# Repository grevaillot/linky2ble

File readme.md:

# linky2ble

stm32wb55 based linky teleinfo to ble bridge - based on https://fumeebleue.fr/ & https://hallard.me/pitinfov12/ designs

## Preview:

## Schematics:

## Aisler project:

https://aisler.net/p/WQYUVWAP (ordering a stencil is recommended :))

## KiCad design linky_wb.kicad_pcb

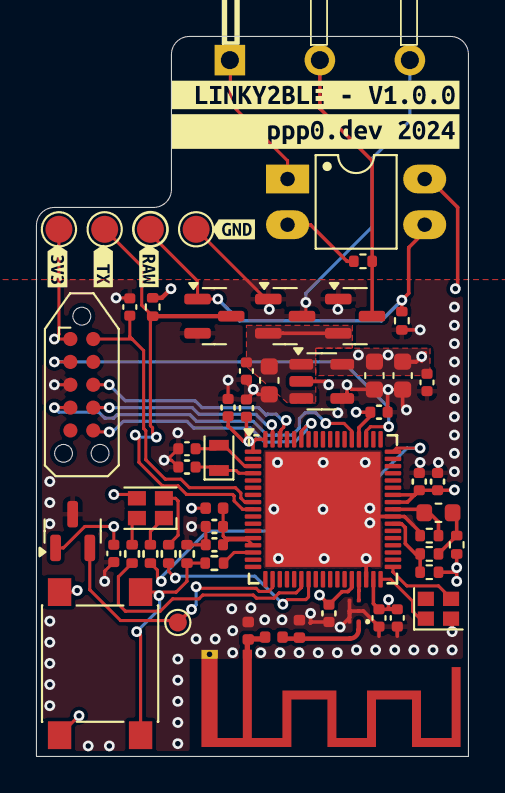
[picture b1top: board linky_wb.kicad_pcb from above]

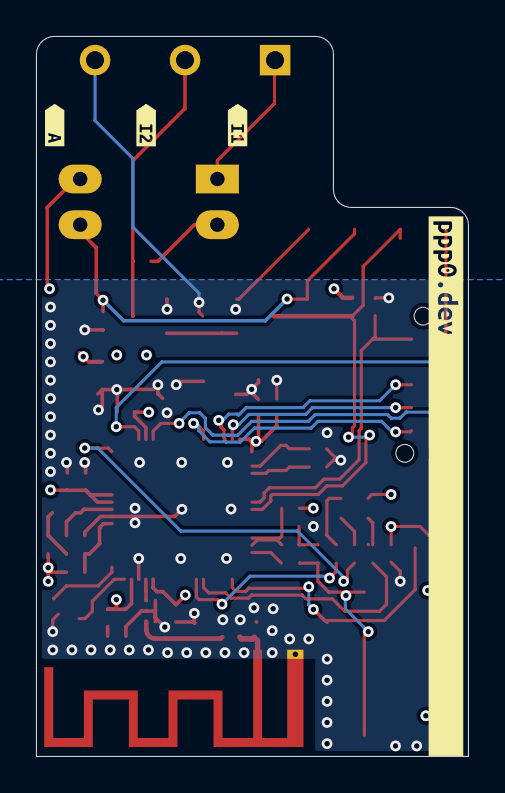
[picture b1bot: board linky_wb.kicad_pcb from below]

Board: 4 copper layers, 24.0 x 40.0 mm, 66 parts (4 on the bottom side), 34 nets.

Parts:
AE2: MLPF-WB55-01E3
AE3: Antenna; Texas_SWRA117D_2.4GHz_Left
C1, C2, C17: 4.7uF; C_0603_1608Metric
C3, C5, C6, C9, C10, C11, C12, C13, C14, C16, C18, C19: 100nF; C_0402_1005Metric
C4: 100pF; C_0402_1005Metric
C7, C8: 10pF; C_0402_1005Metric
C15: 10nF; C_0402_1005Metric
D1, D2: BAT54S; SOT-23
D6: LED_RBAG; LED_Cree-PLCC4_2x2mm_CW
J1: Conn_01x03_Pin; PinHeader_1x03_P2.54mm_Horizontal
J2: Conn_02x05_Counter_Clockwise; Tag-Connect_TC2050-IDC-NL_2x05_P1.27mm_Vertical
L1, L3: tbd; L_0402_1005Metric
L2, L4: 0; L_0402_1005Metric
L5: 1.8nH; L_0603_1608Metric
OC1: LTV-814; DIP-4_W7.62mm_LongPads
Q1: BS170F; SOT-23
R1, R7, R13: 10k; R_0402_1005Metric
R2, R3, R10, R14: 0; R_0402_1005Metric
R4: 2.2; R_0402_1005Metric
R5, R6, R9, R12: 1.5k; R_0402_1005Metric
SW1: SW1; SW_Push_1P1T_NO_6x6mm_H9.5mm
TP1, TP3, TP4, TP6: 5v; TestPoint_Pad_D1.5mm
TP2: TestPoint; TestPoint_Pad_D1.0mm
U1: TPS78230DDC; SOT-23-5
U2: MCP9700AT-ETT; SOT-23
U3: STM32WB55RGVx; QFN-68-1EP_8x8mm_P0.4mm_EP6.4x6.4mm
Y1: nx2012 32.768khz; Crystal_SMD_2012-2Pin_2.0x1.2mm
Y2: NX2016SA 32.0Mhz EXS00A-CS06465; Crystal_SMD_2016-4Pin_2.0x1.6mm
kibuzzard-670CFC0C: G***; kibuzzard-670CFC0C
kibuzzard-670CFC05: G***; kibuzzard-670CFC05
kibuzzard-670CFC68: G***; kibuzzard-670CFC68
kibuzzard-670CFCA8: G***; kibuzzard-670CFCA8
kibuzzard-670D18C1: G***; kibuzzard-670D18C1
kibuzzard-670D18F3: G***; kibuzzard-670D18F3
kibuzzard-670D046C: G***; kibuzzard-670D046C
kibuzzard-670D0302: G***; kibuzzard-670D0302
kibuzzard-670D0308: G***; kibuzzard-670D0308
kibuzzard-670D0311: G***; kibuzzard-670D0311

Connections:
/I1: J1.1, OC1.1
/I2: D1.3, J1.2, R12.2
/button1: R10.2, U3.15 (PA0)
/led_b: R9.1, U3.51 (PA10)
/led_g: R6.1, U3.24 (PA9)
/led_r: R5.1, U3.23 (PA8)
/temp_ana: TP2.1, U2.2 (Vout), U3.19 (PA4)
/tx_linky: Q1.3 (D), R13.2, TP4.1, U3.9 (PC0)
/wb55/ant_path: AE2.1 (OUT), L2.2, L3.2
/wb55/pi_to_ant: AE3.1 (A), L1.2, L2.1
/wb55/rst: C5.1, J2.10, U3.8 (NRST)
/wb55/swclk: J2.4, U3.56 (PA14)
/wb55/swdio: J2.2, U3.54 (PA13)
/wb55/swo: J2.6, U3.63 (PB3)
/wb55/uart_rxd: J2.7, U3.67 (PB7)
/wb55/uart_txd: J2.8, U3.66 (PB6)
/wb55/vdda: C13.1, C15.1, L4.1, U3.13 (VREF+), U3.14 (VDDA)
GND: AE2.2 (GND4), AE2.4 (GND1), AE2.5 (GND2), AE2.6 (GND3), AE3.2 (gnd), C1.2, C2.2, C3.2, C4.2, C5.2, C6.2, C7.2, C8.2, C9.2, C10.2, C11.2, C12.2, C13.2, C14.2, C15.2, C16.2, C17.2, C18.2, C19.2, D1.1, D2.1, D2.3, J1.3, J2.3, L1.1, L3.1, Q1.2 (S), R1.2, R7.2, R14.2, TP6.1, U1.2 (GND), U1.4 (GND), U2.3 (GND), U3.32 (VSSRF), U3.42 (VSSSMPS), U3.69 (VSS), Y2.2
unnamed: AE2.3 (IN), U3.31 (RF1)
unnamed: D6.2 (BK), R5.2
unnamed: D6.4 (GK), R6.2
unnamed: D6.1 (RK), R9.2
unnamed: L5.1, R3.2, R4.2
unnamed: OC1.2, R12.1
unnamed: OC1.3, Q1.1 (G), R1.1, TP3.1
unnamed: R7.1, R10.1, SW1.1
unnamed: U3.35 (OSC_IN), Y2.3
unnamed: U3.34 (OSC_OUT), Y2.1
unnamed: C7.1, U3.3 (PC14), Y1.2
unnamed: C8.1, U3.4 (PC15), Y1.1
unnamed: R2.2, R3.1, U3.41 (VFBSMPS)
unnamed: L5.2, R14.1, U3.43 (VLXSMPS)
VBUS: C2.1, C3.1, D1.2, D2.2, U1.1 (IN), U1.3 (EN)
VDD: C1.1, C4.1, C6.1, C9.1, C10.1, C11.1, C12.1, C14.1, C16.1, C17.1, C18.1, C19.1, D6.3 (A), J2.1, L4.2, OC1.4, R2.1, R4.1, R13.1, SW1.2, TP1.1, U1.5 (OUT), U2.1 (Vdd), U3.1 (VBAT), U3.30 (VDD), U3.33 (VDDRF), U3.44 (VDDSMPS), U3.45 (VDD), U3.55 (VDDUSB), U3.68 (VDD)

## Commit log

2024-10-14 oups, belle pause du midi
2024-10-14 erc/drc: fixes & regen
2024-10-14 schematics: cleanup bom
2024-10-14 1.0.0 boards sent to production
2024-10-15 cleanups, exclude some drcs, fix antenna symbol to avoid ground disconnection, tweak ci

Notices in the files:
parts and their libraries:
Copyright 2021 Accelerated Designs. All rights reserved.
